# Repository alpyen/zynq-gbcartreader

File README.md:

# ZYNQ GBCartReader - Read & Write GameBoy cartridges

This project is aimed to dive into FPGA SoCs and embedded software development
by designing a system that's able to read and write to gameboy cartridges with
a custom designed PCB which interfaces between the FPGA and the game cartridge.

Starting from a very basic bitbanging implementation solely running on the ARM core,
the following design iterations will make use of a more sophisticated architecture
by offloading the board communication to an IP core and moving commands and responses
around with AXI interfaces.

<div align="center">
   
   <br>
   A (badly) handsoldered demonstration of this project with a Pokémon Red cartridge.<br>
   Left is Top, Right is Bottom.
</div>

## Navigation

1. [Supported Cartridge Types](#supported-cartridge-types)
2. [Reading and Writing Cartridges](#reading-and-writing-cartridges)
   1. [Reading ROM / RAM](#reading-rom--ram)
   2. [Writing RAM](#writing-ram)
3. [Setting up the FPGA-board](#setting-up-the-fpga-board)
   1. [Hardware Design with Vivado](#hardware-design-with-vivado)
   2. [Software Application with Vitis](#software-application-with-vitis)
4. [Acknowledgements](#acknowledgements)
5. [Todo-List](#todo-list)

## Supported Cartridge Types

There are a couple of different cartridge types that mostly distinguish between the type of
mapper chip and additional periphery such as RAM, Real-Time-Clock, Battery and more. Here's
a list of the ones that are available:

|  Type  | Status | Verified On                                                                                  |
| :----: | :----: | :------------------------------------------------------------------------------------------- |
| No MBC |   ✅   | Motocross Maniacs (DMG-MX-NOE)<br> Othello (DMG-OT-NOE)                                      |
|  MBC1  |   ✅   | ポケットモンスター 緑 (DMG-APBJ-JPN)<br> Super Mario Land (DMG-ML-NOE)                       |
|  MBC2  |   ✅   | F-1 RACE (DMG-F1-NOE)                                                                        |
|  MBC3  |   ✅   | Pokémon Crystal (CGB-BYTD-NOE)<br> Pokémon Silver (DMG-AAXD-NOE)                             |
|  MBC5  |   ✅   | Pokémon Red (DMG-APAD-NOE)<br> Pokémon Blue (DMG-APED-NOE)<br> Pokémon Yellow (DMG-APSD-NOE) |
| MBC30  |   ✅   | ポケットモンスター クリスタルバージョン (CGB-BXTJ-JPN)                                       |

Some exotic cartridges exist which are not supported. For an exhaustive list check the <a href="https://gbdev.io/pandocs/MBC2.html">Pan Docs</a>
and <a href="https://gbhwdb.gekkio.fi/cartridges/gb.html">GameBoy hardware database</a>. Most games simply use No MBC, MBC1, 3 or 5.
If I own any of the uncommon ones I'll implement them, otherwise I'll skip them as I cannot verify them.

This project supports reading the ROM, reading and writing to RAM allowing you to dump games, backup save files
and also restore save files back to the cartridge. Reading and Writing RTC data is not supported.

I've noted that some games can underreport the number of ROM or RAM banks, for example ポケットモンスター 緑 or ポケットモンスター クリスタルバージョン.
They only report half as many banks present, but manually fixing them in the software dumps these correctly too.

## Reading and Writing Cartridges

This step assumes you have your FPGA-board configured with the application up and running.

Interfacing with the FPGA-board is done through python scripts by sending data over a serial port. Please refer to [Setting up the virutal environment](https://github.com/alpyen/fpga-mediaplayer/blob/main/docs/python.md#setting-up-the-virtual-environment) on how to create a virtual environment and install the pip packages (pyserial) to use the scripts.

The board communicates with a baudrate of `115200` and is plugged in to `/dev/ttyUSB1` on my machine.

Check if your setup is healthy by runing the help command:
```console
(.venv) zynq-gbcartreader/python$ python reader.py -b 115200 -p /dev/ttyUSB1 help
Sending command: help
Receiving data...482B/482B...done!
ZYNQ GBCartReader - Read & Write Gameboy cartridges
written by alpyen - visit the project on github.com/alpyen/zynq-gbcartreader

Available commands:
-------------------
help          Display this help page
parse header  Read cartridge header and parse into readable form
read rom      Read cartridge rom and echo it in binary
read ram      Read cartridge ram (if available) and echo it in binary
write ram     Write cartridge ram (if available) from binary terminal data
```

A help screen should be printed which is sent by the applicaton running on the FPGA-board.
If you do not receive any text or the connection hangs, make sure to correctly flash the board, and check your access permissions on that serial port.

### Reading ROM / RAM

Plugging in a Pokémon Crystal cartridge (CGB-BYTD-NOE) I can read out its header:
```console
(.venv) zynq-gbcartreader/python$ python reader.py -b 115200 -p /dev/ttyUSB1 parse header
Sending command: parse header
Receiving data...858B/858B...done!
Overview:
  Entry Point:       00 C3 6E 01
  Nintendo Logo:     Good
  Title:             PM_CRYSTAL
  Manufac. Code (?): BYTD
  CGB Flag:          CGB exclusive
  New Licensee Code: Nintendo Research & Development 1
  SGB Flag:          No
  Type:              MBC3 + RTC + RAM + Battery
  ROM Size:          2048 KiB (128 banks)
  RAM Size:          32 KiB (4 banks)
  Destination Code:  Overseas
  Old Licensee Code: Check New Licensee Code
  Version:           00
  Header Checksum:   28 (Good)
  Global Checksum:   49 82

Full Header:
  0x0100:  00 C3 6E 01 CE ED 66 66 CC 0D 00 0B 03 73 00 83
  0x0110:  00 0C 00 0D 00 08 11 1F 88 89 00 0E DC CC 6E E6
  0x0120:  DD DD D9 99 BB BB 67 63 6E 0E EC CC DD DC 99 9F
  0x0130:  BB B9 33 3E 50 4D 5F 43 52 59 53 54 41 4C 00 42
  0x0140:  59 54 44 C0 30 31 00 10 06 03 01 33 00 28 49 82
```

Now all you have do to dump this cartridge is to use the `read rom` function. The python script will
output the contents onto `stdout` while printing the current progress onto `stderr`. Pipe the result
into a file like so:
```console
(.venv) zynq-gbcartreader/python$ python reader.py -b 115200 -p /dev/ttyUSB1 read rom > cartridge.gb
Sending command: read rom
Receiving data...2048K/2048K...done!
```

The file extension does not really matter, it is recommended to simply use one that
downstream tools like emulators or inspection tools can handle.

Dumping the cartridge RAM is as straightforward, simply replace `read rom` with `read ram`.

### Writing RAM

Use `write ram` and either pipe in the RAM file or redirect `stdin` like so:
```
(.venv) zynq-gbcartreader/python$ python reader.py -b 115200 -p /dev/ttyUSB1 write ram < cartridge.sav
Sending command: write ram
Sending size...done!
Sending data...32K/32K...done!
```

> Note: Since RTC reads/writes are not implemented some games may ask you to re-set the clock.

## Setting up the FPGA-board

This project was developed with Vivado/Vitis 2025.1 and uses scripts for these versions.
It should be possible to recreate the projects with minimal hassle on different versions.

Currently the PYNQ-Z2 with the software running on the ARM and the Basys3 with the software
running on a MicroBlaze-V soft core processor are supported.

### Hardware Design with Vivado

> Note: This step can be skipped if a pre-built XSA is downloaded from the releases section.
> Place it in the vivado subfolder and continue with the [Vitis](#software-application-with-vitis) section.

You can regenerate the project by starting Vivado and opening the tcl console.
Navigate with `cd` into the vivado subfolder and either run
`source regenerate_pynq_z2.tcl` or `source regenerate_basys3.tcl`.

Vivado will rebuild the project from the source files. Once that's done you can
generate the wrappers for the different block design implementations, synthesize
and export the XSA files for use in Vitis.

> Note: The automatic wrapper generation is not implemented for now.

### Software Application with Vitis

Vitis offers a python interface to dispatch commands from scripts to the application.
In order to use this, you need to source the settings64.sh from the Vitis installation.
If you've installed the Xilinx tools in the default location then open up a new terminal
and load the settings by running these commands based on your operating system:

- Windows: `call C:/Xilinx/2025.1/Vitis/settings64.bat`
- Linux: `source /opt/Xilinx/2025.1/Vitis/settings64.sh`

In the same terminal navigate with `cd` into the vitis subfolder and either run
`vitis -s regenerate.py pynq-z2` or `vitis -s regenerate.py basys3`.

> Note: This script has to be run from Vitis, it will not work with your local python installation.

Unfortunetaly only later versions of Vitis support compilation settings through the
Python API so some entries have to be manually configured for the Basys3 build which
the script will warn you about when creating the Vitis project.

The script takes care of several things:
1. Performs sanity checks to see if the execution environment is correct and if the
   XSA files have been exported, otherwise the platform generation will fail.
2. Delete **everything** except the regenerate.py inside the vitis subfolder to remove
   a potentionally old workspace.
3. Regenerate the different platforms and applications used to run it on the board.
4. Link sources located outside the vitis workspace to into the projects.

Once the regeneration is complete you can open the Vitis GUI and set the workspace
to the vitis subfolder. Now you're ready to build the applications and deploy them.

## Acknowledgements

This project heavily relies on the work of others who have reverse engineered and documented
the inner workings of the Game Boy and its cartridges and/or compiled existing information:
- Pan Docs - https://github.com/gbdev/pandocs
- Game Boy: Complete Technical Reference - https://github.com/Gekkio/gb-ctr

## Todo-List

- Do the actual work in an IP-Core and communicate with PS instead of bitbanging

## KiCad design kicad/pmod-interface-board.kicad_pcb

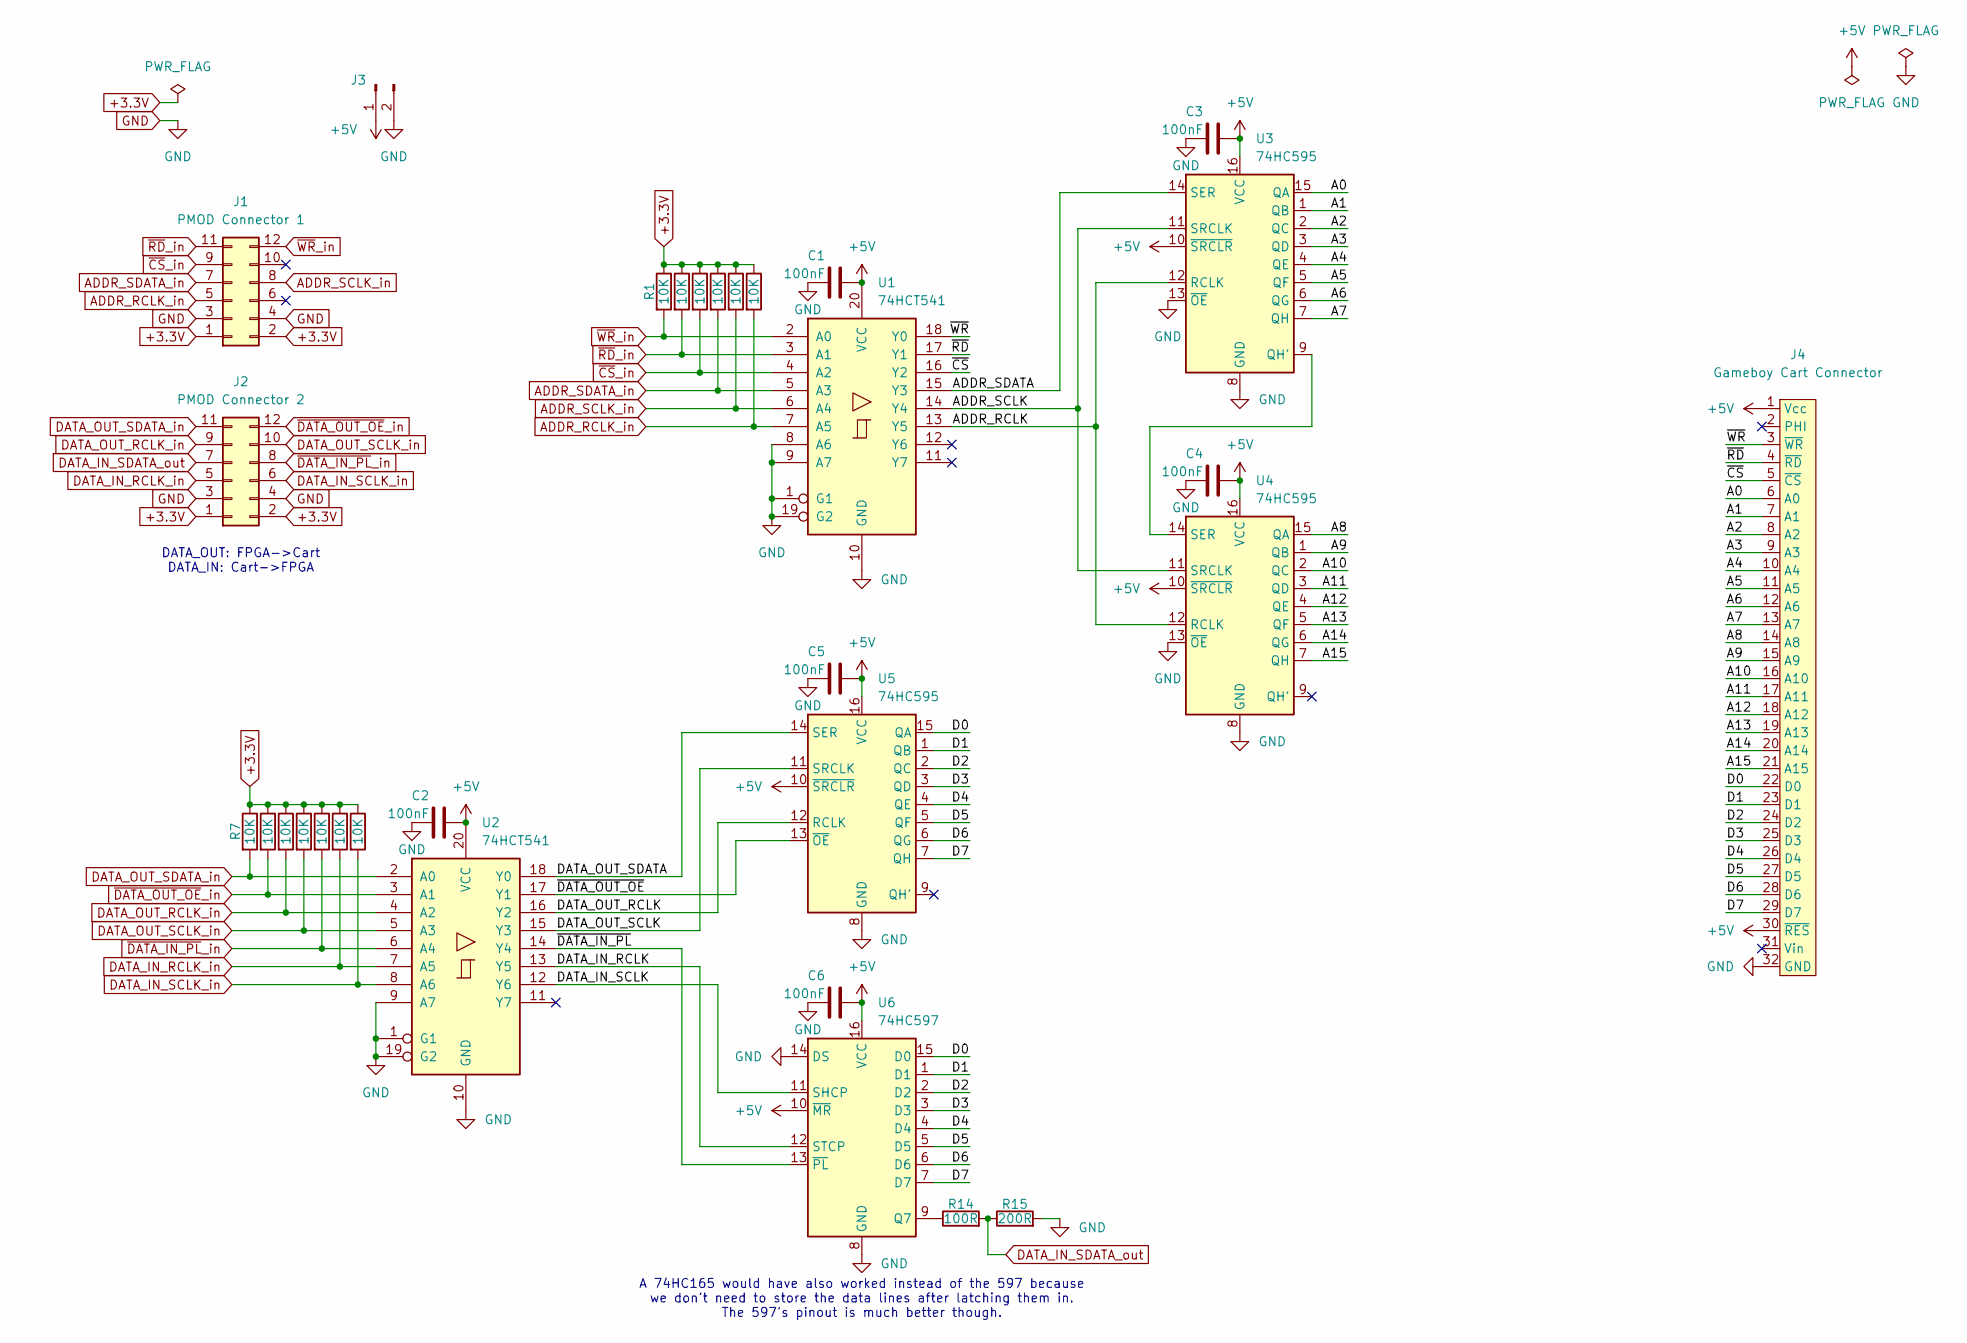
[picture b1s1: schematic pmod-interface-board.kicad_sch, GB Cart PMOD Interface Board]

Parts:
C1, C2, C3, C4, C5, C6: 100nF; C_Disc_D4.7mm_W2.5mm_P5.00mm
J1: PMOD Connector 1; PinHeader_2x06_P2.54mm_Horizontal
J2: PMOD Connector 2; PinHeader_2x06_P2.54mm_Horizontal
J3: PinHeader_1x02_P2.54mm_Vertical
J4: Gameboy Cart Connector; GBCartConnector
R1, R2, R3, R4, R5, R6, R7, R8, R9, R10, R11, R12, R13: 10K; R_Axial_DIN0204_L3.6mm_D1.6mm_P5.08mm_Horizontal
R14: 100R; R_Axial_DIN0204_L3.6mm_D1.6mm_P5.08mm_Horizontal
R15: 200R; R_Axial_DIN0204_L3.6mm_D1.6mm_P5.08mm_Horizontal
U1, U2: 74HCT541; DIP-20_W7.62mm
U3, U4, U5: 74HC595; DIP-16_W7.62mm
U6: 74HC597; DIP-16_W7.62mm

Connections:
+3.3V: J1.1, J1.2, J2.1, J2.2, R1.1, R2.1, R3.1, R4.1, R5.1, R6.1, R7.1, R8.1, R9.1, R10.1, R11.1, R12.1, R13.1
+5V: C1.1, C2.1, C3.1, C4.1, C5.1, C6.1, J3.1, J4.1 (Vcc), J4.30 (~RES), U1.20 (VCC), U2.20 (VCC), U3.10 (~SRCLR), U3.16 (VCC), U4.10 (~SRCLR), U4.16 (VCC), U5.10 (~SRCLR), U5.16 (VCC), U6.10 (~MR), U6.16 (VCC)
/A0: J4.6 (A0), U3.15 (QA)
/A1: J4.7 (A1), U3.1 (QB)
/A2: J4.8 (A2), U3.2 (QC)
/A3: J4.9 (A3), U3.3 (QD)
/A4: J4.10 (A4), U3.4 (QE)
/A5: J4.11 (A5), U3.5 (QF)
/A6: J4.12 (A6), U3.6 (QG)
/A7: J4.13 (A7), U3.7 (QH)
/A8: J4.14 (A8), U4.15 (QA)
/A9: J4.15 (A9), U4.1 (QB)
/A10: J4.16 (A10), U4.2 (QC)
/A11: J4.17 (A11), U4.3 (QD)
/A12: J4.18 (A12), U4.4 (QE)
/A13: J4.19 (A13), U4.5 (QF)
/A14: J4.20 (A14), U4.6 (QG)
/A15: J4.21 (A15), U4.7 (QH)
/ADDR_RCLK: U1.13 (Y5), U3.12 (RCLK), U4.12 (RCLK)
/ADDR_SCLK: U1.14 (Y4), U3.11 (SRCLK), U4.11 (SRCLK)
/ADDR_SDATA: U1.15 (Y3), U3.14 (SER)
/D0: J4.22 (D0), U5.15 (QA), U6.15 (D0)
/D1: J4.23 (D1), U5.1 (QB), U6.1 (D1)
/D2: J4.24 (D2), U5.2 (QC), U6.2 (D2)
/D3: J4.25 (D3), U5.3 (QD), U6.3 (D3)
/D4: J4.26 (D4), U5.4 (QE), U6.4 (D4)
/D5: J4.27 (D5), U5.5 (QF), U6.5 (D5)
/D6: J4.28 (D6), U5.6 (QG), U6.6 (D6)
/D7: J4.29 (D7), U5.7 (QH), U6.7 (D7)
/DATA_IN_RCLK: U2.13 (Y5), U6.12 (STCP)
/DATA_IN_SCLK: U2.12 (Y6), U6.11 (SHCP)
/DATA_OUT_RCLK: U2.16 (Y2), U5.12 (RCLK)
/DATA_OUT_SCLK: U2.15 (Y3), U5.11 (SRCLK)
/DATA_OUT_SDATA: U2.18 (Y0), U5.14 (SER)
/~CS: J4.5 (~CS), U1.16 (Y2)
/~DATA_IN_PL: U2.14 (Y4), U6.13 (~PL)
/~DATA_OUT_OE: U2.17 (Y1), U5.13 (~OE)
/~RD: J4.4 (~RD), U1.17 (Y1)
/~WR: J4.3 (~WR), U1.18 (Y0)
ADDR_RCLK_in: J1.5, R6.2, U1.7 (A5)
ADDR_SCLK_in: J1.8, R5.2, U1.6 (A4)
ADDR_SDATA_in: J1.7, R4.2, U1.5 (A3)
DATA_IN_RCLK_in: J2.5, R12.2, U2.7 (A5)
DATA_IN_SCLK_in: J2.6, R13.2, U2.8 (A6)
DATA_IN_SDATA_out: J2.7, R14.2, R15.1
DATA_OUT_RCLK_in: J2.9, R9.2, U2.4 (A2)
DATA_OUT_SCLK_in: J2.10, R10.2, U2.5 (A3)
DATA_OUT_SDATA_in: J2.11, R7.2, U2.2 (A0)
GND: C1.2, C2.2, C3.2, C4.2, C5.2, C6.2, J1.3, J1.4, J2.3, J2.4, J3.2, J4.32 (GND), R15.2, U1.1 (G1), U1.8 (A6), U1.9 (A7), U1.10 (GND), U1.19 (G2), U2.1 (G1), U2.9 (A7), U2.10 (GND), U2.19 (G2), U3.8 (GND), U3.13 (~OE), U4.8 (GND), U4.13 (~OE), U5.8 (GND), U6.8 (GND), U6.14 (DS)
unnamed: U3.9 (QH'), U4.14 (SER)
unnamed: R14.1, U6.9 (Q7)
~CS_in: J1.9, R3.2, U1.4 (A2)
~DATA_IN_PL_in: J2.8, R11.2, U2.6 (A4)
~DATA_OUT_OE_in: J2.12, R8.2, U2.3 (A1)
~RD_in: J1.11, R2.2, U1.3 (A1)
~WR_in: J1.12, R1.2, U1.2 (A0)

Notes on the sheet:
A 74HC165 would have also worked instead of the 597 because we don't need to store the data lines after latching them in. The 597's pinout is much better though.
DATA_OUT: FPGA->Cart DATA_IN: Cart->FPGA

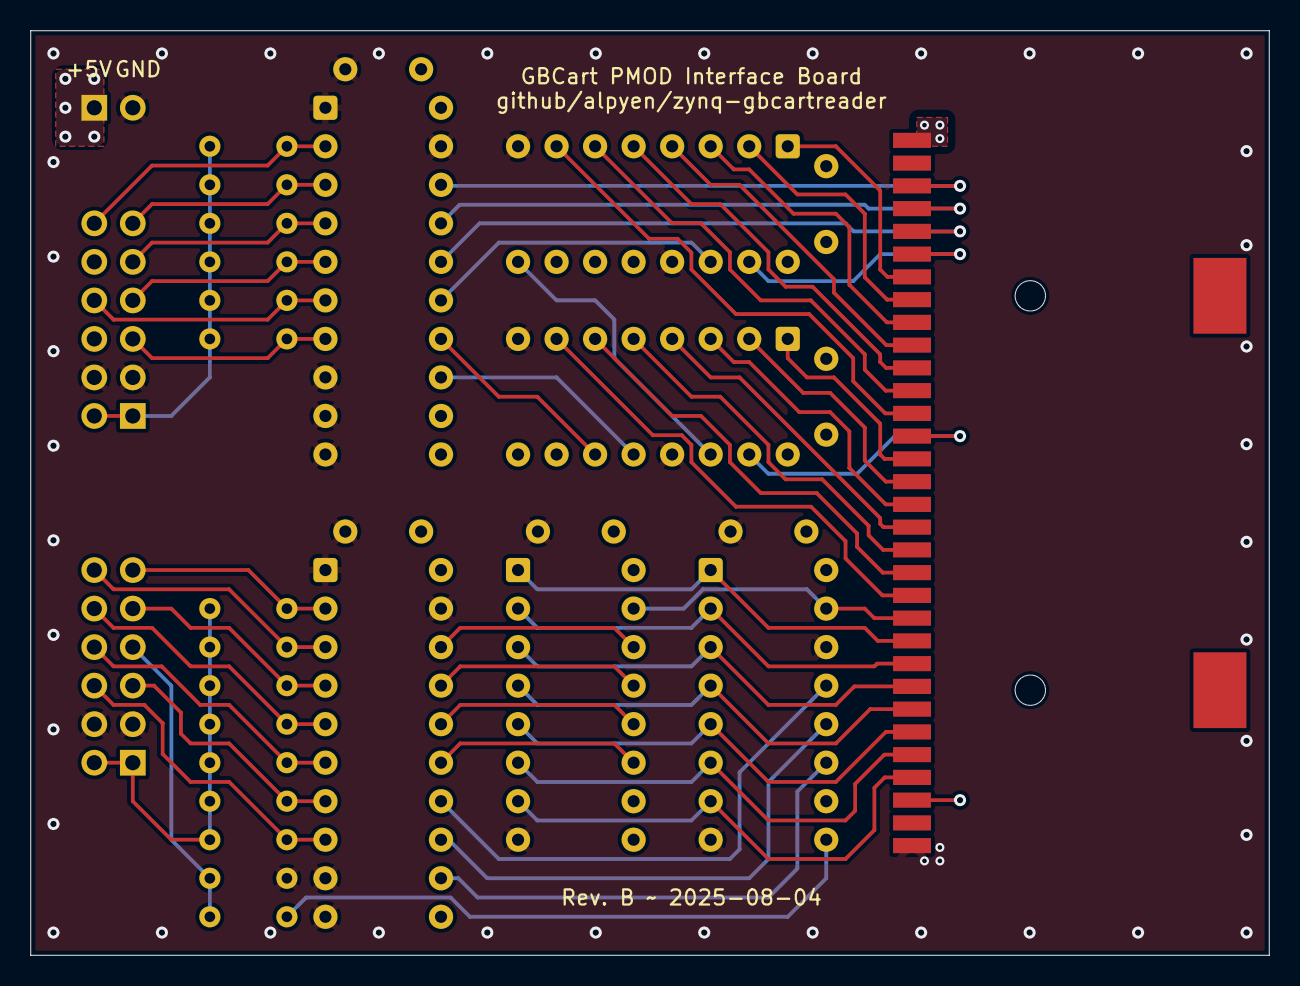
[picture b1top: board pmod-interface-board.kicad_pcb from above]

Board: 4 copper layers, 81.7 x 61.0 mm, 31 parts (0 on the bottom side), 56 nets.

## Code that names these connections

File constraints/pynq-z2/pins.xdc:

# PmodA

set_property -dict { PACKAGE_PIN Y18   IOSTANDARD LVCMOS33 } [get_ports { pmods_tri_io[0] }]; # RDn
set_property -dict { PACKAGE_PIN Y19   IOSTANDARD LVCMOS33 } [get_ports { pmods_tri_io[1] }]; # CSn
set_property -dict { PACKAGE_PIN Y16   IOSTANDARD LVCMOS33 } [get_ports { pmods_tri_io[2] }]; # ADDR_SDATA
set_property -dict { PACKAGE_PIN Y17   IOSTANDARD LVCMOS33 } [get_ports { pmods_tri_io[3] }]; # ADDR_RCLK
set_property -dict { PACKAGE_PIN U18   IOSTANDARD LVCMOS33 } [get_ports { pmods_tri_io[4] }]; # WRn
# set_property -dict { PACKAGE_PIN U19   IOSTANDARD LVCMOS33 } [get_ports { ja[5] }]; # x
set_property -dict { PACKAGE_PIN W18   IOSTANDARD LVCMOS33 } [get_ports { pmods_tri_io[5] }]; # ADDR_SCLK
# set_property -dict { PACKAGE_PIN W19   IOSTANDARD LVCMOS33 } [get_ports { ja[7] }]; # x

# PmodB

set_property -dict { PACKAGE_PIN W14   IOSTANDARD LVCMOS33 } [get_ports { pmods_tri_io[6] }]; # DATA_OUT_SDATA
set_property -dict { PACKAGE_PIN Y14   IOSTANDARD LVCMOS33 } [get_ports { pmods_tri_io[7] }]; # DATA_OUT_RCLK
set_property -dict { PACKAGE_PIN T11   IOSTANDARD LVCMOS33 } [get_ports { pmods_tri_io[8] }]; # DATA_IN_SDATA
set_property -dict { PACKAGE_PIN T10   IOSTANDARD LVCMOS33 } [get_ports { pmods_tri_io[9] }]; # DATA_IN_RCLK
set_property -dict { PACKAGE_PIN V16   IOSTANDARD LVCMOS33 } [get_ports { pmods_tri_io[10] }]; # DATA_OUT_OE
set_property -dict { PACKAGE_PIN W16   IOSTANDARD LVCMOS33 } [get_ports { pmods_tri_io[11] }]; # DATA_OUT_SCLK
set_property -dict { PACKAGE_PIN V12   IOSTANDARD LVCMOS33 } [get_ports { pmods_tri_io[12] }]; # DATA_IN_PL
set_property -dict { PACKAGE_PIN W13   IOSTANDARD LVCMOS33 } [get_ports { pmods_tri_io[13] }]; # DATA_IN_SCLK

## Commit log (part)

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2025-07-22 kicad: started work on the pmod interface board
2025-07-23 kicad: finished interface board schematics
2025-07-25 kicad: added decoupling caps
2025-07-26 kicad: changed schematics pmod gnd/3v3 labeling
2025-07-26 kicad: moved pins for better connectivity and renamed srclk to sclk
2025-07-29 kicad: added custom gbcart connector footprint and updated schematics
2025-07-29 kicad: adjusted footprint center
2025-07-29 kicad: fixed resistor footprints
2025-07-29 kicad: board setup and initial parts placement
    Board setup maybe has to be changed further down the line.
2025-07-29 kicad: fixed footprint by changing margin outline to courtyard
    Otherwise it would not floodfill underneath it.
2025-07-30 kicad: routing completed, sped up resistor divider by lowering values
2025-07-30 kicad: switched out power header and moved pmod connectors closer
2025-07-30 kicad: changed +5v/gnd layer fill so it passes through the tht legs
2025-07-30 kicad: pcb excess shortened
2025-07-30 kicad: added copper pour and vias to cart vcc/gnd
2025-07-30 kicad: silkscreen work on the backside
2025-07-31 kicad: centered decoupling caps to ics and fixed routing
2025-08-01 kicad: moved resistor divider and added gnd stitching vias
2025-08-01 kicad: adjusted silkscreen for better manufacturing
2025-08-01 kicad: narrowed thermal relief spokes and added copper pour to +5v header
2025-08-01 kicad: added keepout zone to make the cart connections more appealing
    There were less than a handful of GND fill between some of these traces so we might aswell just remove them so it looks better. Should have little to no impact on performance.
    Also adjusted the GND via pour to make it symmetric to the +5V one.
2025-08-01 kicad: added revision and date silkscreen - board is complete
2025-08-04 kicad: fixed faulty 597 wiring and moved pullups to +3.3v
2025-08-08 docs: updated readme with project description
2025-08-16 vivado: created project with software implementation design
    Another block design for the hardware implementation will be added later when the software implementation is complete.
    The wrappers have to be generated and removed manually for now.
2025-08-16 vitis: created software implementation project and regenerate.py
    The actual functionality is not implemented yet, only the git work is done.
2025-08-16 docs: updated main readme with regeneration/build instructions
2025-08-18 src: extracted functionality into separate files and updated regenerate script
2025-08-18 docs: added wip message to readme
2025-08-20 src: sw_impl: added basic command prompt to standalone app
2025-08-20 src: renaming and refactoring standalone application files
2025-08-20 src/kicad: fixed incorrectly named OE and PL pins to ~OE and ~PL
2025-08-20 src: sw_impl: fixed incorrect pmod initialization
    Now the correct data line is set as an input and the default values are written before exiting the tri-state.
    This way we don't run into the risk of breaking or corrupting the cartridge.
2025-08-27 src: sw_impl: added pmod read and minor refactoring
    - Moved cartridge buffer to cartridge.cpp where it actually belongs.
    - Replaced the GPIO define address in init_pmod with the function parameter.
    - Added sleeps to slow down PMOD toggle rate otherwise the cartridge cannot handle it.
2025-08-27 src: sw_impl: mbc1 bank reading implemented and works on board
    - Read routine only tailored to MBC1
    - Other MBCs have different layouts and need separate routines
    - Before implementing other MBCs, the source code should be organized in a good way - namespaces maybe?
2025-08-28 src: sw_impl: refactor mbc code into namespaces
2025-08-28 src: sw_impl: added mbc5 ram+rom reading and mbc detection
2025-08-28 src: sw_impl: refactored visible/hidden mbc members and removed trailing whitespaces
2025-08-28 src: sw_impl: added echo command to show/hide prompt
2025-08-28 python: added script to dump cartridges from the standalone implementations
2025-08-28 src: sw_impl: removed incompatible cartridge types from ram reading
2025-08-28 python: added num bytes received info to console output
2025-08-28 src: sw_impl: added mbc3 rom and ram reading
    Reading RTC data is the next goal as it's important for some games.
2025-08-29 src: sw_impl: added mbc3 rtc reading
2025-08-29 python: added requirements and minor comment changes
2025-08-31 src: sw_impl: added mbc3 write ram, works on hardware too but needs rework
    While it also works flawlessly on the hardware I'm not happy with the way it is implemented now. There has to be some sort of flow-control to not overrun the RX buffer on the Zynq.
    This will only be necessary for the standalone implementation so we need to #ifdef the relevant parts?
2025-09-01 src: sw_impl: removed echoing, rewriting code for python/uart
    Since the linuxapp is supposed to share most of the code with with the standalone app it is important to organize the code correctly.
    However the python/uart frontend is not complete yet, so we will implement this completely first, and when it's time to work on the linuxapp the boundaries / common code will be much clearer so we ca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
2025-09-01 docs: added acknowledgements to readme
2025-09-01 src: sw_impl: extracted definitions to thin out "parse header"
2025-09-19 src: sw_impl: added rom only reading (no mbc)
2025-09-25 docs: added pcb pictures to readme
2025-09-25 docs: added supported cartridge type section to readme
2025-09-25 src: added mbc5 write ram
2025-09-28 src: sw_impl: added latching before rtc read, wip rtc write
    The data in the RTC registers updated even before latching them. That's strange as it should not happen automatically.
2025-10-17 src: revised uart protocol
    Now each party knows how many bytes are being transmitted so they can timeout if something bad happens.
2025-10-18 src: cartridge: moved reset to beginning of operation
2025-10-18 src: cli_handlers changed byte xil_printf to sendbyte
2025-10-18 src: changed out from uart0 to stdout (same)
2025-10-18 src: replaced vsprintf with own xil_sprintf to reduce binary size by ~20K
    The implementation is just a copy of the existing xil_printf but passing a char** to fill and advance, rather than to output it straight to console.
2025-10-18 src: merged xil_printf into xil_sprintf
2025-11-22 python: refactored reader script and fixed timeout bug
2025-12-05 src: cli_handlers removed compiler intrinsic for compile time string length
2025-12-05 src: made uart_readline more concise
2025-12-05 src: cartridge: changed mbc3/5 write_ram to use _shiftout_data
2025-12-05 misc: removed unnecessary struct, updated readme
2025-12-05 src: sw_impl: added mbc1 read/write ram (unverified)
    It's very similar to MBC3 and the sources are detailed on this.
    I expect it to work, however it remains unverified for now.
2025-12-07 src: sw_impl: added mbc2 read rom
2025-12-07 src: sw_impl: added mbc2 read/write ram
2026-05-09 src: minor touch ups
2026-05-11 src: removed rtc commands
    The PCB has PHI floating so MBC3 cartridges aren't accessed properly. A new board revision could fix this.
2026-06-07 readme: added mbc30 and updated mbc list with new games
    ポケットモンスター クリスタルバージョン (Pokémon Crystal) reports back as MBC3 (since there is no MBC30 entry) but has twice the RAM banks.
    ポケットモンスター 緑 (Pokémon Green) has a dead battery so MBC1 is not fully verified for now, it will be after replacing it.
    Interestingly the cartridge reports only 32 ROM banks instead of 64, force-reading 64 banks dumps the ROM correctly, otherwise only the first half is read.
